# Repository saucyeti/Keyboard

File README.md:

\# Keyboard Project

\~65% wired keyboard on ATMEGA32U4

16MHz clock

0 detent 24 pulse rotary encoder w/switch

I2C OLED display

A few programmable macros

Running QMK firmware

## Visuals

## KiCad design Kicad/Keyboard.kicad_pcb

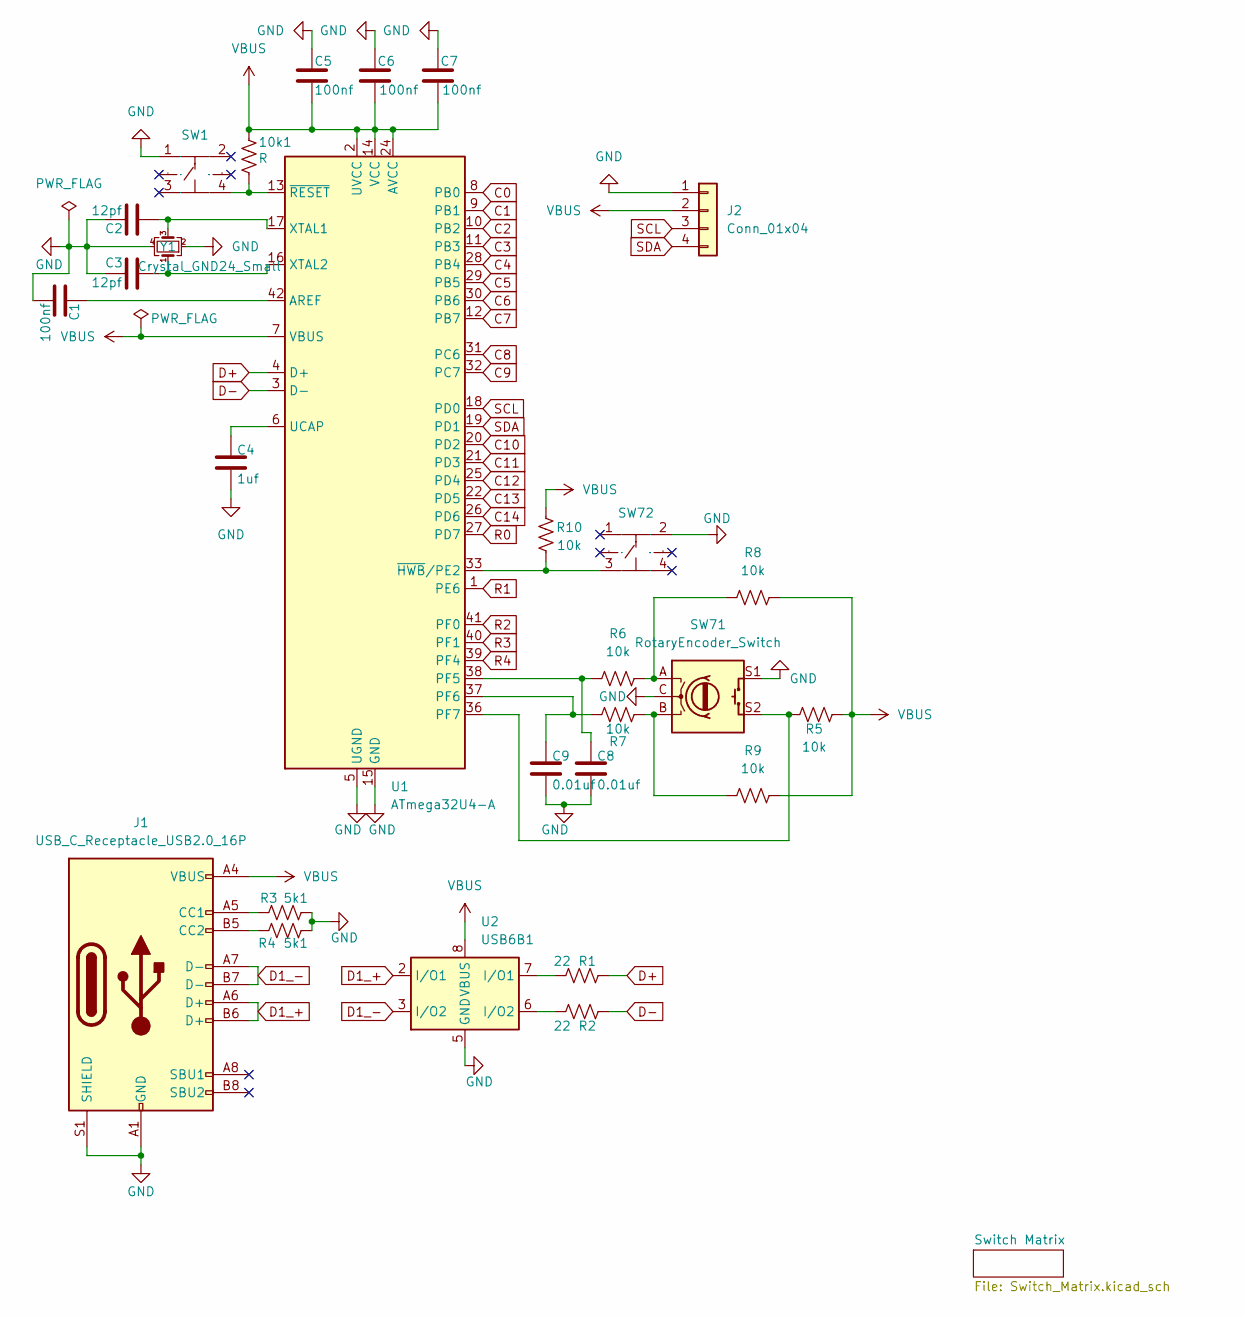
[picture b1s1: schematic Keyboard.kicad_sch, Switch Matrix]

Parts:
10k1: R; R_0402_1005Metric_Pad0.72x0.64mm_HandSolder
C1, C5, C6, C7: 100nf; C_01005_0402Metric_Pad0.57x0.30mm_HandSolder
C2, C3: 12pf; C_01005_0402Metric_Pad0.57x0.30mm_HandSolder
C4: 1uf; C_01005_0402Metric_Pad0.57x0.30mm_HandSolder
C8, C9: 0.01uf; C_01005_0402Metric_Pad0.57x0.30mm_HandSolder
J1: USB_C_Receptacle_USB2.0_16P; USB_C_Receptacle_G-Switch_GT-USB-7010ASV
J2: Conn_01x04; OLED-TH_L38.0-W12.0_HS91L02W2C01
R1, R2: 22; R_0402_1005Metric_Pad0.72x0.64mm_HandSolder
R3, R4: 5k1; R_0402_1005Metric_Pad0.72x0.64mm_HandSolder
R5, R6, R7, R8, R9, R10: 10k; R_0402_1005Metric_Pad0.72x0.64mm_HandSolder
SW1, SW72: Pushbuttonthing; Manufacturer Part Pushbutton
SW71: RotaryEncoder_Switch; RotaryEncoder_Alps_EC11E-Switch_Vertical_H20mm_CircularMoun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
U1: ATmega32U4-A; TQFP-44_10x10mm_P0.8mm
U2: USB6B1; SOIC-8_3.9x4.9mm_P1.27mm
Y1: Crystal_GND24_Small; Crystal_SMD_3225-4Pin_3.2x2.5mm_HandSoldering

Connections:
C0: U1.8 (PB0); also elsewhere on the board
C1: U1.9 (PB1); also elsewhere on the board
C2: U1.10 (PB2); also elsewhere on the board
C3: U1.11 (PB3); also elsewhere on the board
C4: U1.28 (PB4); also elsewhere on the board
C5: U1.29 (PB5); also elsewhere on the board
C6: U1.30 (PB6); also elsewhere on the board
C7: U1.12 (PB7); also elsewhere on the board
C8: U1.31 (PC6); also elsewhere on the board
C9: U1.32 (PC7); also elsewhere on the board
C10: U1.20 (PD2); also elsewhere on the board
C11: U1.21 (PD3); also elsewhere on the board
C12: U1.25 (PD4); also elsewhere on the board
C13: U1.22 (PD5); also elsewhere on the board
C14: U1.26 (PD6); also elsewhere on the board
D1_+: J1.A6 (D+), J1.B6 (D+), U2.2 (I/O1)
D1_-: J1.A7 (D-), J1.B7 (D-), U2.3 (I/O2)
D+: R1.2, U1.4 (D+)
D-: R2.1, U1.3 (D-)
GND: C1.2, C2.2, C3.2, C4.2, C5.1, C6.1, C7.1, C8.2, C9.2, J1.A1 (GND), J1.A12 (GND), J1.B1 (GND), J1.B12 (GND), J1.S1 (SHIELD), J2.1, R3.1, R4.2, SW1.1, SW71.C, SW71.S1, SW72.2, U1.5 (UGND), U1.15 (GND), U1.23 (GND), U1.35 (GND), U1.43 (GND), U2.4 (GND), U2.5 (GND), Y1.2, Y1.4
unnamed: J1.A5 (CC1), R3.2
unnamed: J1.B5 (CC2), R4.1
unnamed: R1.1, U2.7 (I/O1)
unnamed: R2.2, U2.6 (I/O2)
unnamed: R6.2, R8.1, SW71.A
unnamed: R7.2, R9.1, SW71.B
unnamed: C1.1, U1.42 (AREF)
unnamed: C8.1, R6.1, U1.38 (PF5)
unnamed: C9.1, R7.1, U1.37 (PF6)
unnamed: R5.1, SW71.S2, U1.36 (PF7)
unnamed: C4.1, U1.6 (UCAP)
unnamed: C2.1, U1.17 (XTAL1), Y1.3
unnamed: C3.1, U1.16 (XTAL2), Y1.1
unnamed: R10.2, SW72.3, U1.33 (~HWB/PE2)
unnamed: 10k1.2, SW1.4, U1.13 (~RESET)
R0: U1.27 (PD7); also elsewhere on the board
R1: U1.1 (PE6); also elsewhere on the board
R2: U1.41 (PF0); also elsewhere on the board
R3: U1.40 (PF1); also elsewhere on the board
R4: U1.39 (PF4); also elsewhere on the board
SCL: J2.3, U1.18 (PD0)
SDA: J2.4, U1.19 (PD1)
VBUS: 10k1.1, C5.2, C6.2, C7.2, J1.A4 (VBUS), J1.A9 (VBUS), J1.B4 (VBUS), J1.B9 (VBUS), J2.2, R5.2, R8.2, R9.2, R10.1, U1.2 (UVCC), U1.7 (VBUS), U1.14 (VCC), U1.24 (AVCC), U1.34 (VCC), U1.44 (AVCC), U2.1 (VBUS), U2.8 (VBUS)

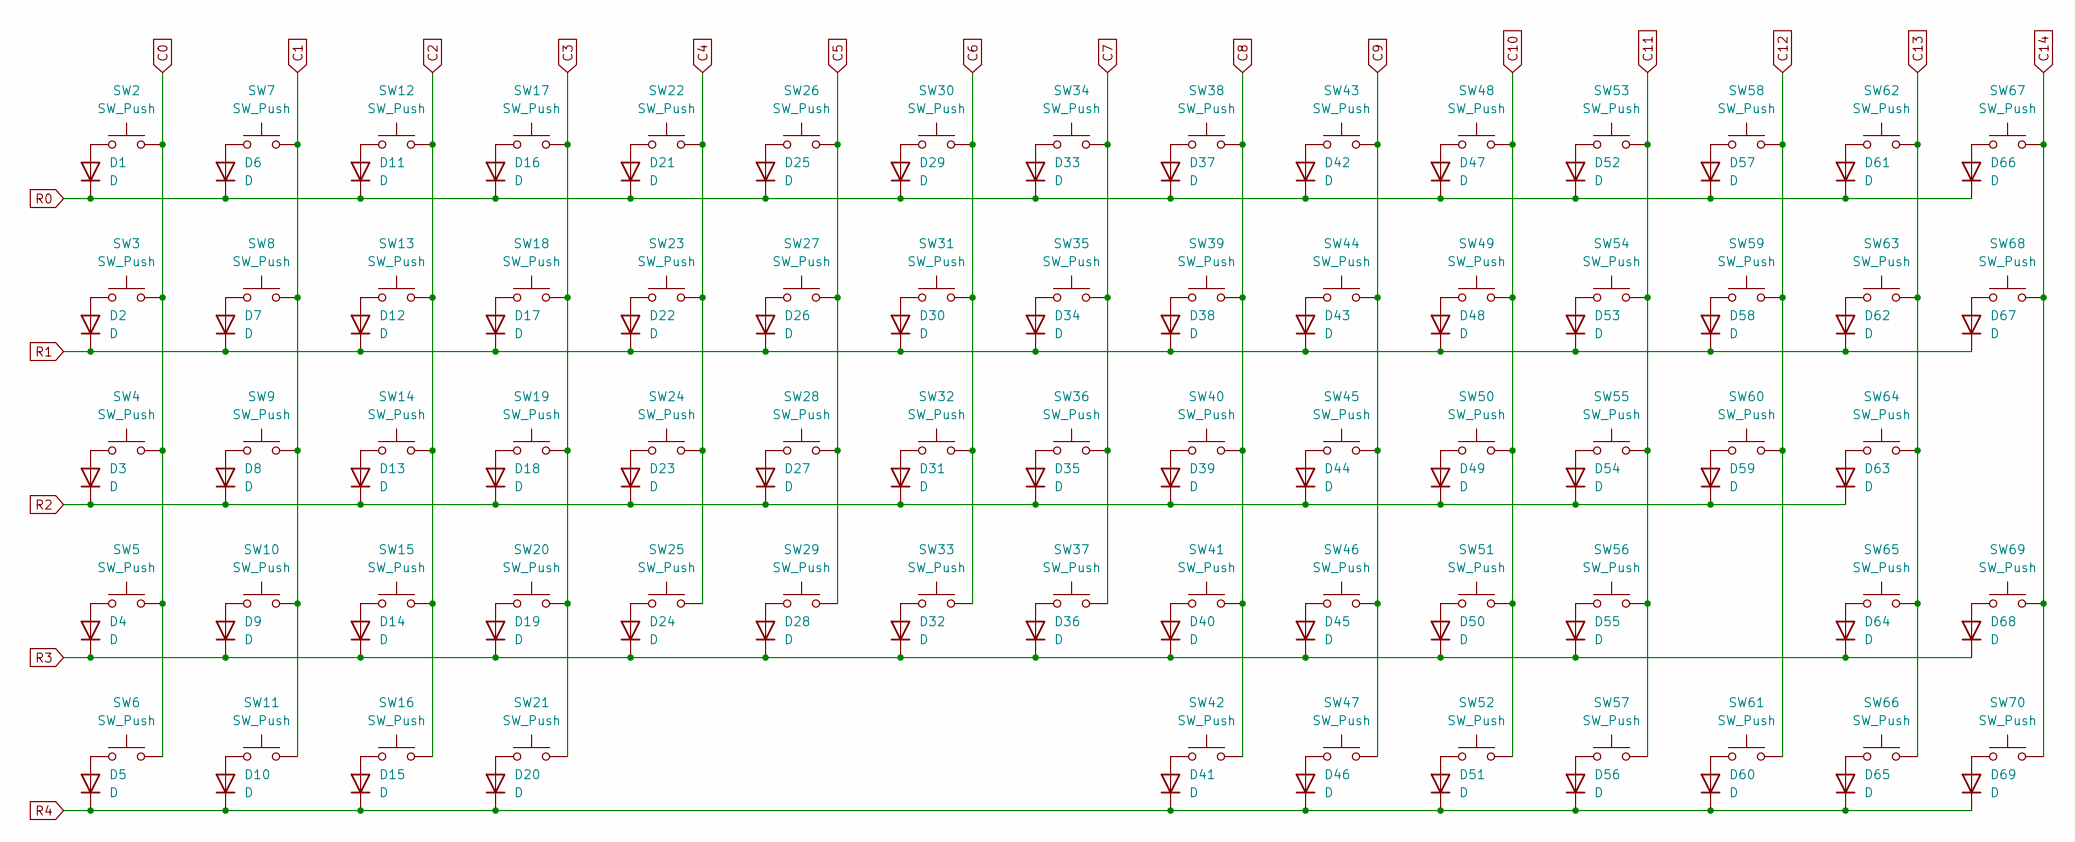
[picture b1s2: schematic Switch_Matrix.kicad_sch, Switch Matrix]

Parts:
D1, D2, D3, D4, D5, D6, D7, D8, D9, D10, D11, D12, D13, D14, D15, D16, D17, D18, D19, D20, D21, D22, D23, D24, D25, D26, D27, D28, D29, D30, D31, D32, D33, D34, D35, D36, D37, D38, D39, D40, D41, D42, D43, D44, D45, D46, D47, D48, D49, D50, D51, D52, D53, D54, D55, D56, D57, D58, D59, D60, D61, D62, D63, D64, D65, D66, D67, D68, D69: D; D_SOD-323F
SW2, SW7, SW8, SW9, SW10, SW12, SW13, SW14, SW15, SW17, SW18, SW19, SW20, SW22, SW23, SW24, SW25, SW26, SW27, SW28, SW29, SW30, SW31, SW32, SW33, SW34, SW35, SW36, SW37, SW38, SW39, SW40, SW41, SW42, SW43, SW44, SW45, SW46, SW47, SW48, SW49, SW50, SW51, SW52, SW53, SW54, SW55, SW57, SW58, SW59, SW61, SW64, SW65, SW66, SW67, SW68, SW69, SW70: SW_Push; SW_Cherry_MX_PCB_1.00u
SW3, SW63: SW_Push; SW_Cherry_MX_PCB_1.50u
SW4: SW_Push; SW_Cherry_MX_PCB_1.75u
SW5, SW60: SW_Push; SW_Cherry_MX_PCB_2.25u
SW6, SW11, SW16: SW_Push; SW_Cherry_MX_PCB_1.25u
SW21: SW_Push; SW_Cherry_MX_PCB_6.25u
SW56: SW_Push; SW_Cherry_MX_PCB_2.75u
SW62: SW_Push; SW_Cherry_MX_PCB_2.00u

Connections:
C0: SW2.2, SW3.2, SW4.2, SW5.2, SW6.2; also elsewhere on the board
C1: SW7.2, SW8.2, SW9.2, SW10.2, SW11.2; also elsewhere on the board
C2: SW12.2, SW13.2, SW14.2, SW15.2, SW16.2; also elsewhere on the board
C3: SW17.2, SW18.2, SW19.2, SW20.2, SW21.2; also elsewhere on the board
C4: SW22.2, SW23.2, SW24.2, SW25.2; also elsewhere on the board
C5: SW26.2, SW27.2, SW28.2, SW29.2; also elsewhere on the board
C6: SW30.2, SW31.2, SW32.2, SW33.2; also elsewhere on the board
C7: SW34.2, SW35.2, SW36.2, SW37.2; also elsewhere on the board
C8: SW38.2, SW39.2, SW40.2, SW41.2, SW42.2; also elsewhere on the board
C9: SW43.2, SW44.2, SW45.2, SW46.2, SW47.2; also elsewhere on the board
C10: SW48.2, SW49.2, SW50.2, SW51.2, SW52.2; also elsewhere on the board
C11: SW53.2, SW54.2, SW55.2, SW56.2, SW57.2; also elsewhere on the board
C12: SW58.2, SW59.2, SW60.2, SW61.2; also elsewhere on the board
C13: SW62.2, SW63.2, SW64.2, SW65.2, SW66.2; also elsewhere on the board
C14: SW67.2, SW68.2, SW69.2, SW70.2; also elsewhere on the board
unnamed: D1.2 (A), SW2.1
unnamed: D2.2 (A), SW3.1
unnamed: D3.2 (A), SW4.1
unnamed: D4.2 (A), SW5.1
unnamed: D5.2 (A), SW6.1
unnamed: D6.2 (A), SW7.1
unnamed: D7.2 (A), SW8.1
unnamed: D8.2 (A), SW9.1
unnamed: D9.2 (A), SW10.1
unnamed: D10.2 (A), SW11.1
unnamed: D11.2 (A), SW12.1
unnamed: D12.2 (A), SW13.1
unnamed: D13.2 (A), SW14.1
unnamed: D14.2 (A), SW15.1
unnamed: D15.2 (A), SW16.1
unnamed: D16.2 (A), SW17.1
unnamed: D17.2 (A), SW18.1
unnamed: D18.2 (A), SW19.1
unnamed: D19.2 (A), SW20.1
unnamed: D20.2 (A), SW21.1
unnamed: D21.2 (A), SW22.1
unnamed: D22.2 (A), SW23.1
unnamed: D23.2 (A), SW24.1
unnamed: D24.2 (A), SW25.1
unnamed: D25.2 (A), SW26.1
unnamed: D26.2 (A), SW27.1
unnamed: D27.2 (A), SW28.1
unnamed: D28.2 (A), SW29.1
unnamed: D29.2 (A), SW30.1
unnamed: D30.2 (A), SW31.1
unnamed: D31.2 (A), SW32.1
unnamed: D32.2 (A), SW33.1
unnamed: D33.2 (A), SW34.1
unnamed: D34.2 (A), SW35.1
unnamed: D35.2 (A), SW36.1
unnamed: D36.2 (A), SW37.1
unnamed: D37.2 (A), SW38.1
unnamed: D38.2 (A), SW39.1
unnamed: D39.2 (A), SW40.1
unnamed: D40.2 (A), SW41.1
unnamed: D41.2 (A), SW42.1
unnamed: D42.2 (A), SW43.1
unnamed: D43.2 (A), SW44.1
unnamed: D44.2 (A), SW45.1
unnamed: D45.2 (A), SW46.1
unnamed: D46.2 (A), SW47.1
unnamed: D47.2 (A), SW48.1
unnamed: D48.2 (A), SW49.1
unnamed: D49.2 (A), SW50.1
unnamed: D50.2 (A), SW51.1
unnamed: D51.2 (A), SW52.1
unnamed: D52.2 (A), SW53.1
unnamed: D53.2 (A), SW54.1
unnamed: D54.2 (A), SW55.1
unnamed: D55.2 (A), SW56.1
unnamed: D56.2 (A), SW57.1
unnamed: D57.2 (A), SW58.1
unnamed: D58.2 (A), SW59.1
unnamed: D59.2 (A), SW60.1
unnamed: D60.2 (A), SW61.1
unnamed: D61.2 (A), SW62.1
unnamed: D62.2 (A), SW63.1
unnamed: D63.2 (A), SW64.1
unnamed: D64.2 (A), SW65.1
unnamed: D65.2 (A), SW66.1
unnamed: D66.2 (A), SW67.1
unnamed: D67.2 (A), SW68.1
unnamed: D68.2 (A), SW69.1
unnamed: D69.2 (A), SW70.1
R0: D1.1 (K), D6.1 (K), D11.1 (K), D16.1 (K), D21.1 (K), D25.1 (K), D29.1 (K), D33.1 (K), D37.1 (K), D42.1 (K), D47.1 (K), D52.1 (K), D57.1 (K), D61.1 (K), D66.1 (K); also elsewhere on the board
R1: D2.1 (K), D7.1 (K), D12.1 (K), D17.1 (K), D22.1 (K), D26.1 (K), D30.1 (K), D34.1 (K), D38.1 (K), D43.1 (K), D48.1 (K), D53.1 (K), D58.1 (K), D62.1 (K), D67.1 (K); also elsewhere on the board
R2: D3.1 (K), D8.1 (K), D13.1 (K), D18.1 (K), D23.1 (K), D27.1 (K), D31.1 (K), D35.1 (K), D39.1 (K), D44.1 (K), D49.1 (K), D54.1 (K), D59.1 (K), D63.1 (K); also elsewhere on the board
R3: D4.1 (K), D9.1 (K), D14.1 (K), D19.1 (K), D24.1 (K), D28.1 (K), D32.1 (K), D36.1 (K), D40.1 (K), D45.1 (K), D50.1 (K), D55.1 (K), D64.1 (K), D68.1 (K); also elsewhere on the board
R4: D5.1 (K), D10.1 (K), D15.1 (K), D20.1 (K), D41.1 (K), D46.1 (K), D51.1 (K), D56.1 (K), D60.1 (K), D65.1 (K), D69.1 (K); also elsewhere on the board

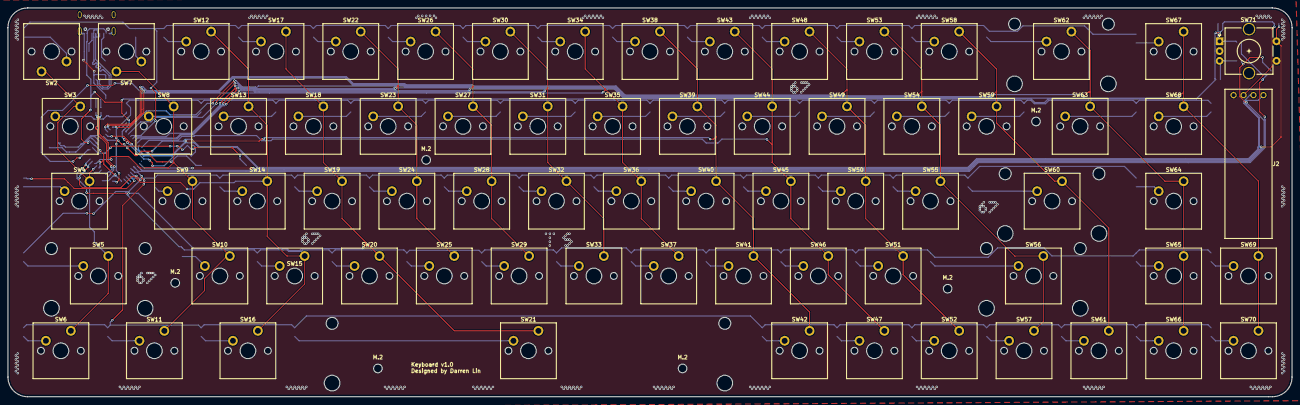
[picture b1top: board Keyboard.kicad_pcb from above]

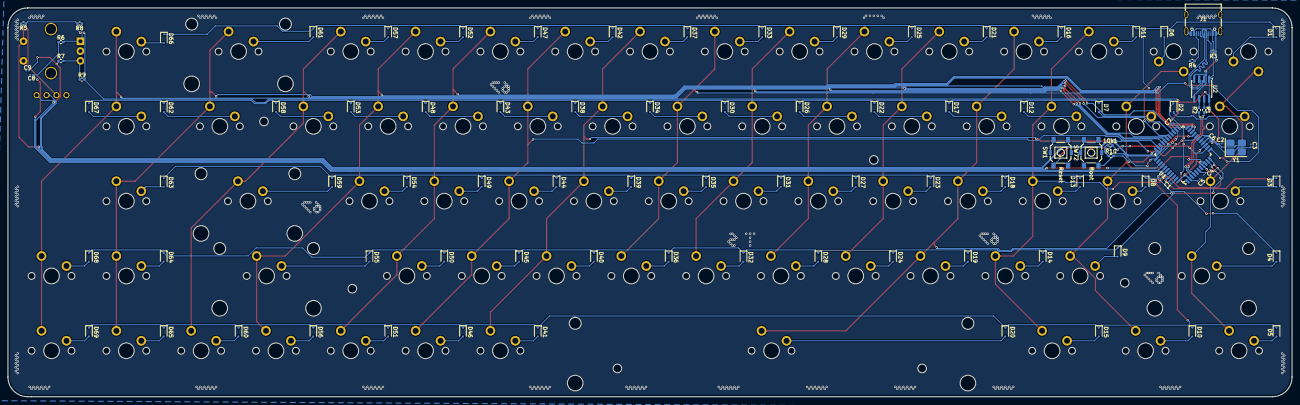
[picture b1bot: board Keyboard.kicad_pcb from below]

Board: 2 copper layers, 327.0 x 99.0 mm, 172 parts (95 on the bottom side), 112 nets.

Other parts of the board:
M.2, M.2#2, M.2#3, M.2#4, M.2#5, M.2#6: MountingHole_2.2mm_M2_ISO14580

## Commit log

2026-04-09 init
2026-04-09 fix names
2026-04-09 name fix
2026-04-09 folders
2026-04-10 add encoder + hardware debouncing
2026-04-10 encoder layout + fix footprint
2026-04-10 added bootloader
2026-04-11 cancer traces
2026-04-16 updated bootloader and reset footprints + symbols + reroute traces
2026-04-17 traces
2026-04-17 routed all traces
2026-04-18 added ground planes + fixed DRC errors/warnings
2026-04-18 mounting holes
2026-04-19 fixed edge cuts/mounting holes + board review
2026-04-20 differential routing + board review
2026-04-20 fix mounting holes finalizing stuff
2026-04-20 readme update
2026-04-20 readme
2026-04-20 final draft fr fr
2026-04-20 gerbers + step files
2026-04-20 final gerber fr fr
2026-04-20 final gerber fr fr fr
2026-04-20 actually final gerber fr fr fr fr
2026-04-22 caught huge mcu i2c issue
2026-04-22 reroute traces + final final final final final gerbers
2026-06-01 stitching vias
2026-06-01 stitching vias ++
2026-06-01 Gerberts
2026-06-17 added stitching vias
